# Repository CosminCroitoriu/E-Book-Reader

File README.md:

Nume: Croitoriu Cosmin-Mircea  
Grupă: 332CB

# TSC Project - OpenBook E-Book Reader
Overview
-
This diagram illustrates the hardware architecture of the OpenBook E-Reader, an ESP32-based electronic paper reading device. The system is built around the ESP32-C6-WROOM-1 microcontroller, which interfaces with a 7.5-inch e-Paper display, environmental sensors, and user input buttons.  

***Key Components:*** 

* Core Processing: ESP32-C6 microcontroller with integrated Wi-Fi 6 and BLE 5
* Display: 800×480 resolution e-Paper display connected via SPI
* Sensors: BME688 for temperature, humidity, pressure, and air quality monitoring via I2C
* Power: 2500mAh LiPo battery with fuel gauge and USB-C charging
* Storage: SD card interface for e-book storage via SPI
* Timekeeping: DS3231 RTC with backup power
* User Interface: Buttons via 3xGPIO
* Expansion: QWIIC/Stemma connector for additional peripherals

The firmware is built on FreeRTOS and includes specialized modules for display management, sensor monitoring, battery management, user interface, and e-book rendering. This modular architecture ensures flexible development, easy maintenance, and power-efficient operation—essential for an e-reader device with long battery life requirements.

Power Consumption
-

* In active reading mode (display updated occasionally): ~15-30mA
* In display update mode: ~50-100mA temporarily
* In Wi-Fi active mode: ~120-180mA
* In sleep mode: ~1-5mA
* In deep sleep mode: <50µA

With a 2500mAh battery, the device can operate approximately:

* 100-150 hours in active reading mode (without Wi-Fi)
* 15-20 hours with Wi-Fi constantly active
* Up to 1500 hours (2 months) in deep sleep mode

ESP32-C6 Pin Assignments
-
| Connection Name |   GPIO / Pin Name  | Function  |
|-----------------|------------------|-------------------------------------------------|
| **3V3**         | IO 8             | 3.3V Power line                        |
| **EN (Reset)**  | EN              | Reset Button   |           
| **USB_D-**      | IO12            | USB Data negative, communication  | 
| **USB_D+**      | IO13            | USB Data positive, communication  |
| **Buton Boot**  | IO9             | Bootbutton  |    
| **Buton Change**| IO15            | User input for state changing  |
| **TX (UART)**   | TXD0 / GPIO16   | Serial Transmitter (UART) for communication  |
| **RX (UART)**   | RXD0 / GPIO17   | Serial Receiver (UART) for communication  |
| **SCK (SPI)**   | IO6             | SPI Clock for clock synchronization |
| **MOSI (SPI)**  | IO7             | Transmitter between MC and the Flash, SD Card and display |
| **MISO (SPI)**  | IO2             | Receiver between MC and the Flash, SD Card and display |
| **FLASH_CS**    | IO11            | Flash Chip Select |
| **EPD_CS**      | IO10            | Display Chip select |
| **EPD_DC**      | IO5             | Display Command |
| **EPD_RST**     | IO23            | Display Reset |
| **EPD_BUSY**    | IO3             | Busy Display Signal |
| **SDA (I2C)**   | IO21            | Bidirectional Communication RTC, BME688, Battery Gauge |
| **SCL (I2C)**   | IO22            | I2C synchronization |
| **SS_SD**       | IO4             | SD Card Chip Select |
| **I2C_PW**      | IO19            | Power Control on I2C |
| **EPD_3V3_C**   | IO20            | 3.3V Power Line for the Display |
| **32KHZ**       | IO1             | 32kHz Signal Input |
| **INT_RTC**     | IO0             | RTC DS3231 Interrupt |
| **RTC_RST**     | IO18            | External Reset RTC | 

Bill of Materials
-

| Component | Value | Assigned Part | Where to buy | Datasheet |
| ---------- | --------- | --------- | ---------- | ----- |
| Resistor | 15	$\Omega$ | R_CAPACITOR | [Buy](https://ro.mouser.com/ProductDetail/YAGEO/RT0402FRE0715RL?qs=BXCcY9r%252B08DFFpLSkPOIqQ%3D%3D) | [Datasheet](https://ro.mouser.com/datasheet/2/447/PYu_RT_1_to_0_01_RoHS_L_15-3461507.pdf) |
| Resistor | 200 $\Omega$ | R1_BAT | [Buy](https://ro.mouser.com/ProductDetail/Vishay-Beyschlag/MCS0402MD2000BE100?qs=3SvaY9RawMJNVte4F12%252BZQ%3D%3D) | [Datasheet](https://www.vishay.com/doc?28952) |
| Resistor | 100k $\Omega$ | R_PWRUSB | [Buy](https://ro.mouser.com/ProductDetail/Vishay-Beyschlag/MCT0603PD1003DP500?qs=5aG0NVq1C4wWAn8Ei3OpZA%3D%3D) | [Datasheet](https://www.vishay.com/doc?28916) |
| Resistor | 10k $\Omega$ | R1, R1_PINH1, R1_PINH2, R2-PINH1, R2_PINH2, R4, R5, R6, R7, R8, R9, R10, R_BOOT, R_CHANGE, R_CL1, R_RESET | [Buy](https://ro.mouser.com/ProductDetail/Vishay-Beyschlag/MCS0402MD1002BE000?qs=17u8i%2FzlE8%2F9BrAaXkMk1w%3D%3D) | [Datasheet](https://www.vishay.com/doc?28952) |
| Resistor | 0.47 $\Omega$ | R3 | [Buy](https://ro.mouser.com/ProductDetail/SEI-Stackpole/CSR0402JKR470?qs=IPgv5n7u5QawIB6nBEt8wA%3D%3D) | [Datasheet](https://ro.mouser.com/datasheet/2/385/SEI_CSR_CSRN-3077593.pdf) |
| Resistor |  2k $\Omega$ | R2_BAT |[Buy](https://ro.mouser.com/ProductDetail/Vishay-Beyschlag/MCS04020C2001FE000?qs=wTZ%2FFzl837YG0wIkZJJOwQ%3D%3D) | [Datasheet](https://www.vishay.com/doc?28705) |
| Resistor | 2.2 $\Omega$ | R2 | [Buy](https://ro.mouser.com/ProductDetail/SEI-Stackpole/RMCF0402FT2R20?qs=IPgv5n7u5QbBgyl0jwhwsA%3D%3D) | [Datasheet](https://ro.mouser.com/datasheet/2/385/SEI_RMCF_RMCP-3077565.pdf) |
| Resistor | 5k1 $\Omega$ | R1_USB, R2_USB | [Buy](https://www.venkel.com/part/TFCR0603-16W-K-5690FT) | [Datasheet](https://data.venkel.com/documents/tfcr-series?_gl=1*tdo8m*_ga*NTA1MTc5MTcyLjE3NDM4OTMzNjc.*_ga_JRKGBZNVM8*MTc0Mzg5MzM2Ni4xLjAuMTc0Mzg5MzM2OC41OC4wLjA.) |
| Capacitor | 10uF | C6 | [Buy](https://ro.mouser.com/ProductDetail/Samsung-Electro-Mechanics/CL10A106KQ8NNNL?qs=xZ%2FP%252Ba9zWqaes9JKSsob2Q%3D%3D) | [Datasheet](https://ro.mouser.com/datasheet/2/585/MLCC-1837944.pdf) |
| Capacitor | 1uF/50V | EPD_C3 | [Buy](https://ro.mouser.com/ProductDetail/KYOCERA-AVX/06035D105MAT2A?qs=k4kUdCzLgS5%252BURKe1SOIeQ%3D%3D) | [Datasheet](https://ro.mouser.com/datasheet/2/40/cx5r_KGM-3223198.pdf) |
| Capacitor | 4.7uF | C1_BAT, C1_BAT1, C2_BAT, C2_BAT1, C4_USB | [Buy](https://ro.mouser.com/ProductDetail/KYOCERA-AVX/0402ZD475MAT2A?qs=NBFAU1oqP4W4U2PCPHI0sg%3D%3D) | [Datasheet](https://ro.mouser.com/datasheet/2/40/cx5r_KGM-3223198.pdf) |
| Capacitor | 100nF | C1, C2, C3_USB, C5, C7, C8, C9, C_DELAY | [Buy](https://ro.mouser.com/ProductDetail/KYOCERA-AVX/06033G104ZAT2A?qs=NXubJDmysXJMPmHfVo6Z%252BA%3D%3D) | [Datasheet](https://ro.mouser.com/datasheet/2/40/KGM_Y5V-3223189.pdf) |
| PFMF.050.1 | - | PFMF.050.1 | [Buy](https://ro.mouser.com/ProductDetail/Schurter/PFMF.050.2?qs=1auRipcfynCums5v1iucSA%3D%3D) |  [Datasheet](https://ro.mouser.com/datasheet/2/358/typ_PFMF-1275918.pdf) |
| USB4110-GF-A | - | J2 | [Buy](https://ro.mouser.com/ProductDetail/GCT/USB4110-GF-A?qs=KUoIvG%2F9IlYiZvIXQjyJeA%3D%3D) | [Datasheet](https://ro.mouser.com/datasheet/2/837/GCT_USB4110_Product_Drawing___20k_cycles-3455479.pdf) |
| USBLC6-2SC6Y | - | D1 | [Buy](https://ro.mouser.com/ProductDetail/STMicroelectronics/USBLC6-2SC6Y?qs=gNDSiZmRJS%2FOgDexvXkdow%3D%3D) | [Datasheet](https://ro.mouser.com/datasheet/2/389/usblc6_2sc6y-1852505.pdf) |
| SD0805S020S1R0 | - | D2, D7| [Buy](https://ro.mouser.com/ProductDetail/KYOCERA-AVX/SD0805S020S1R0?qs=jCA%252BPfw4LHbpkAoSnwrdjw%3D%3D) | [Datasheet](https://ro.mouser.com/datasheet/2/40/schottky-3165252.pdf) |
| DMG2305UX-7 | - | Q1, Q2 | [Buy](https://ro.mouser.com/ProductDetail/Diodes-Incorporated/DMG2305UX-7?qs=L1DZKBg7t5F%2FNBHrjfxC%252Bg%3D%3D) | [Datasheet](https://www.diodes.com/assets/Datasheets/DMG2305UX.pdf) |
| XC6220A331MR-G | - | U5 | [Buy](https://ro.mouser.com/ProductDetail/Torex-Semiconductor/XC6220A331MR-G?qs=AsjdqWjXhJ8ZSWznL1J0gg%3D%3D) | [Datasheet](https://ro.mouser.com/datasheet/2/760/xc6220-3371556.pdf) |
| Capacitor | 100 uF TANT | C_TANT | [Buy](https://ro.mouser.com/ProductDetail/KYOCERA-AVX/TAJW107M010RNJ?qs=Wtp%252Bf%2FAeVqIH8v1VxV%252B1Rg%3D%3D) | [Datasheet](https://ro.mouser.com/datasheet/2/40/TAJ-3165264.pdf) |
| 112A-TAAR-R03_ATTEND | - | J4 | [Buy](https://www.digikey.ro/en/products/detail/attend-technology/112A-TAAR-R03/17633923) | [Datasheet](https://www.attend.com.tw/data/download/file/112A-TAAR-R03_Spec.pdf)
| ESP32-C6-WROOM-1-N8 | - | U1 | [Buy](https://ro.mouser.com/ProductDetail/Espressif-Systems/ESP32-C6-WROOM-1-N8?qs=8Wlm6%252BaMh8ST02Gmwp74cw%3D%3D) | [Datasheet](https://ro.mouser.com/datasheet/2/891/Espressif_ESP32_C6_WROOM_1__Datasheet_V0_1_PRELIMI-3239987.pdf) |
| MCP73831 | - | U7 | [Buy](https://ro.mouser.com/ProductDetail/Microchip-Technology/MCP73831T-2ACI-OT?qs=yUQqVecv4qvbBQBGbHx0Mw%3D%3D) | [Datasheet](https://ro.mouser.com/datasheet/2/268/MCP73831_Family_Data_Sheet_DS20001984H-3441711.pdf) |
| CHG_LED | - | CHG_LED | [Buy](https://store.comet.srl.ro/Catalogue/Product/40478/) | [Datasheet](https://www.snapeda.com/parts/KP-1608SURCK/Kingbright/datasheet/) |
| SI1308EDL-T1-GE3 | - | Q3 | [Buy](https://ro.mouser.com/ProductDetail/Vishay-Semiconductors/SI1308EDL-T1-GE3?qs=bX1%252BNvsK%2FBramh9tgpOaEw%3D%3D) | [Datasheet](https://www.vishay.com/doc?63399) |
| MBR0530 | - | D3, D4, D5 | [Buy](https://ro.mouser.com/ProductDetail/Micro-Commercial-Components-MCC/MBR0530-T?qs=9VyI4qLX4NTSXkb9ynzJnA%3D%3D) | [Datasheet](https://ro.mouser.com/datasheet/2/258/mcc_mbr0520~mbr0560sod123-1179695.pdf) |
| Power Inductor | 68uH | L1 | [Buy](https://ro.mouser.com/ProductDetail/Wurth-Elektronik/744043680?qs=PGXP4M47uW6VkZq%252BkzjrHA%3D%3D) | [Datasheet](https://www.we-online.com/components/products/datasheet/744043680.pdf) |
| FH34SRJ-24S-0.5SH | - | J1 | [Buy](https://ro.mouser.com/ProductDetail/Hirose-Connector/FH34SRJ-24S-0.5SH99?qs=vcbW%252B4%252BSTIpKBl5ap9J8Fw%3D%3D) | [Datasheet](https://ro.mouser.com/datasheet/2/185/FH34SRJ_24S_0_5SH_99__CL0580_1255_6_99_2DDrawing_0-1615044.pdf) |
| BME688 Sensor | - | U8 | [Buy](https://ro.mouser.com/ProductDetail/Bosch-Sensortec/BME688?qs=IS%252B4QmGtzzqQoVDscqwx3A%3D%3D) | [Datasheet](https://ro.mouser.com/datasheet/2/783/bst_bme688_fl000-2307034.pdf) |
| BD5229G-TR | - | U6 |[Buy](https://ro.mouser.com/ProductDetail/ROHM-Semiconductor/BD5229G-TR?qs=4kLU8WoGk0vvnhrrYwdszw%3D%3D) | [Datasheet](https://fscdn.rohm.com/en/products/databook/datasheet/ic/power/voltage_detector/bd52xxg-e.pdf) |
| PTS841 Button | - | BOOT_BUTTON, CHANGE_BUTTON, RESET_BUTTON | [Buy](https://ro.mouser.com/ProductDetail/CK/PTS841-ESD-GKP-SMTR-LFS?qs=d0WKAl%252BL4KbeUlwuiSQZWA%3D%3D) | [Datasheet](https://www.ckswitches.com/media/2805/pts841.pdf) |
| MAX17048G+T10 | - | U2 | [Buy](https://ro.mouser.com/ProductDetail/Analog-Devices-Maxim-Integrated/MAX17048G%2bT10?qs=D7PJwyCwLAoGnnn8jEPRBQ%3D%3D) | [Datasheet](https://ro.mouser.com/datasheet/2/609/MAX17048_MAX17049-3469099.pdf) |
| W25Q512JVEIQ | - | U4 | [Buy](https://ro.mouser.com/ProductDetail/Winbond/W25Q512JVEIQ?qs=l7cgNqFNU1jw6svr3at6tA%3D%3D) | [Datasheet](https://ro.mouser.com/datasheet/2/949/Winbond_W25Q512JV_Datasheet-3240039.pdf) |
| PGB1010603MR | - | D6, D8, D9, D10, D11, D12 | [Buy](https://ro.mouser.com/ProductDetail/Littelfuse/PGB1010603MRHF?qs=KvZd0dN2Zg%2FuIq6icj%252BGKA%3D%3D) | [Datasheet](https://www.littelfuse.com/media?resourcetype=datasheets&itemid=8a337998-d54d-466b-be4e-dc5bcd1f9321&filename=littelfuse_pulseguard_pgb1_datasheet.pdf) |
| QWIIC_RIGHT_ANGLE | - | J3 | [Buy](https://ro.mouser.com/ProductDetail/GCT/USB4110-GF-A?qs=KUoIvG%2F9IlYiZvIXQjyJeA%3D%3D) | [Datasheet](https://ro.mouser.com/datasheet/2/837/GCT_USB4110_Product_Drawing___20k_cycles-3455479.pdf) |
| DS3231SN | - | U3 | [Buy](https://ro.mouser.com/ProductDetail/Analog-Devices-Maxim-Integrated/DS3231SN?qs=ffX8NcjNb2RmKAb9wAk9Ug%3D%3D) | [Datasheet](https://ro.mouser.com/datasheet/2/609/DS3231-3421123.pdf) |
| CPH3225A | - | C_SUPERCAP | [Buy](https://ro.mouser.com/ProductDetail/Seiko-Semiconductors/CPH3225A?qs=3etwrb1wR%252BhUOph6lAO7eg%3D%3D) | [Datasheet](https://ro.mouser.com/datasheet/2/360/Seiko_Instruments_MicroBattery_E_20230330_2024Jan_-3561061.pdf) |

Design Considerations
-

* The modular design allows for individual component updates and easy problem diagnosis
* Using a single LDO regulator to generate 3.3V for the entire board simplifies the power design
* Battery charging is done through the USB-C port, ensuring wide compatibility
* The environmental sensors allow for monitoring the conditions in which the device is used and can be used to alert the user about unfavorable conditions
* Used a predefined 3D model for the screen. Source: https://grabcad.com/library/7-5in-e-ink-display-assortment-1

PCB Observations
-

* PCB Dieletctric layer has been reduced from 1.6mm to 1mm to fit in the case.
* Via Stitching has been applied around the MC, so the impedance of the ground plane is lowered.

Errors and Warnings
- 
* The Board Outline Clearence errors were all approved, as every component was matching the placement in the given document.
* Unconnected Lines warnings are a bug from Fusion, as everytime I try to remove them, the error reappears. 
* Copper Width errors for the inductor were approved as the model matched the one in the givne scheme.

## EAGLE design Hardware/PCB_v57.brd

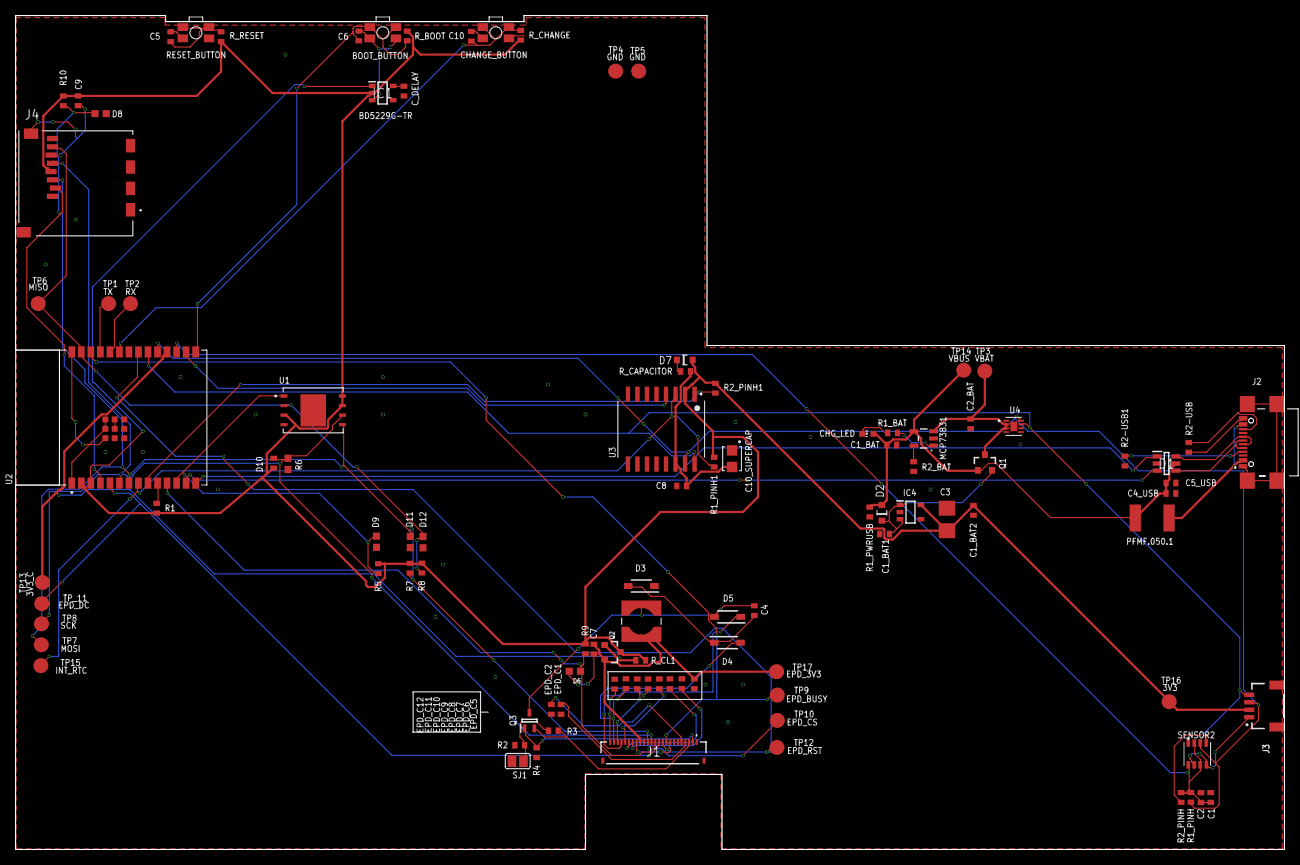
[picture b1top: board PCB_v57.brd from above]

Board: 2 copper layers, 169.2 x 111.2 mm, 103 parts (0 on the bottom side), 56 nets.

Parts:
BOOT_BUTTON: BUTTON_CUSYOMV1; MYBUTTON
C1, C2, C4_USB, C6, C8, C9, C10: 100nF; EAGLE-LTSPICE_C0402
C1_BAT, C1_BAT1, C1_BAT2, C2_BAT, C5_USB: 4.7uF; EAGLE-LTSPICE_C0402
C3: 100uF TANT; RCL_CT3528
C4: 4.7uF/25V; EAGLE-LTSPICE_C0402
C5: 1uF; EAGLE-LTSPICE_C0402
C7: 10uF; EAGLE-LTSPICE_C0402
C10_SUPERCAP: CPH3225A; CAPCP3225X100N
CHANGE_BUTTON: BUTTON_CUSYOMV1; MYBUTTON
CHG_LED: ADAFRUIT_CHIP-LED0603
C_DELAY: 100nF; EAGLE-LTSPICE_C0402
D1: USBLC6-2SC6Y; SOT95P280X145-6N
D2, D7: ESP32_WROVER_AVX---SD0805S020S1R0_AVX_SD0805S020S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; ESP32_WROVER_AVX---SD0805S020S1R0_AVX_SD0805S020S1R0_0
D3, D4, D5: MBR0530; SOD3716X135N
D6, D8, D9, D10, D11, D12: PGB1010603MR; DIOC1608X36N
EPD_C1, EPD_C2, EPD_C6, EPD_C7, EPD_C8, EPD_C9, EPD_C10, EPD_C11, EPD_C12: 1uF/50V; EAGLE-LTSPICE_C0402
EPD_C5: 01.uF/50V; EAGLE-LTSPICE_C0402
IC1: BD5229G-TR; SOT95P280X125-5N
IC4: XC6220A331MR-G; SOT95P280X120-5N
J1: FH34SRJ-24S-0.5SH_99_; FH34SRJ24S05SH99
J2: SAMACSYS_PARTS_USB4110-GF-A; SAMACSYS_PARTS_USB4110GFA
J3: QWIIC_RIGHT_ANGLE; JST04_1MM_RA
J4: 112A-TAAR-R03_ATTEND; 112ATAARR03ATTEND
L1: 68uH; IND_4828-WE-TPC_WRE
MCP73831: ESP32_WROVER_SPARKFUN-IC-POWER_MCP73831; ESP32_WROVER_SPARKFUN-IC-POWER_SOT23-5
PFMF.050.1: ESP32C6_VARISTORCN1812; ESP32C6_VARISTOR_CT/CN1812
Q1, Q2: 20V/4.2A/52mΩ/1.4W; ESP32_WROVER_SPARKFUN-DISCRETESEMI_SOT23-3
Q3: SI1308EDL-T1-GE3; SOT65P210X110-3N
R1, R1_PINH, R2_PINH, R4: 10k; ESP32_WROVER_EAGLE-LTSPICE_R0402
R1_BAT: 200; ESP32_WROVER_EAGLE-LTSPICE_R0402
R1_PINH1, R2_PINH1, R5, R6, R7, R8, R9, R10: 10K; ESP32_WROVER_EAGLE-LTSPICE_R0402
R1_PWRUSB: 100K; ESP32_WROVER_EAGLE-LTSPICE_R0402
R2: 2.2; ESP32_WROVER_EAGLE-LTSPICE_R0402
R2-USB, R2-USB1: 5k1; ESP32_WROVER_EAGLE-LTSPICE_R0402
R2_BAT: 2K; ESP32_WROVER_EAGLE-LTSPICE_R0402
R3: 0.47; ESP32_WROVER_EAGLE-LTSPICE_R0402
RESET_BUTTON: BUTTON_CUSYOMV1; MYBUTTON
R_BOOT: 10K; ESP32_WROVER_EAGLE-LTSPICE_R0402
R_CAPACITOR: 15; ESP32_WROVER_EAGLE-LTSPICE_R0402
R_CHANGE: 10K; ESP32_WROVER_EAGLE-LTSPICE_R0402
R_CL1: 10k; ESP32_WROVER_EAGLE-LTSPICE_R0402
R_RESET: 10K; ESP32_WROVER_EAGLE-LTSPICE_R0402
SENSOR2: ESP32_WROVER_BME680_BME680; ESP32_WROVER_BME680_PSON80P300X300X100-8N
SJ1: SJ
TP1, TP2, TP3, TP4, TP5, TP6, TP7, TP8, TP9, TP10, TP12, TP13, TP14, TP15, TP16, TP17: TPTP20R; TP20R
TP_11: TPTP20R; TP20R
U1: W25Q512JVEIQ; SON127P600X800X80-9N
U2: ESP32-C6-WROOM-1-N8; XCVR_ESP32-C6-WROOM-1-N8
U3: DS3231SN#; SOIC127P1032X265-16N
U4: MAX17048G+T10; SON50P200X200X80-9N

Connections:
3V3: C1_BAT2.2, C3.+, C9.1, D7.2, IC1.2, IC4.5, J3.2, J4.P4, Q2.3, R1.2, R1_PINH1.2, R2_PINH1.2, R5.2, R6.2, R7.2, R8.2, R9.2, R10.2, R_BOOT.2, R_CHANGE.2, R_CL1.2, R_RESET.2, TP16.TP, U1.3, U1.7, U1.8, U2.2, U3.2
32KHZ: R2_PINH1.1, U2.9, U3.1
DN: D1.4, J2.A7, J2.B7
DP: D1.6, J2.A6, J2.B6
EPD_3V3: C7.1, EPD_C5.2, J1.15, J1.16, L1.2, Q2.2, TP17.TP
EPD_3V3_C: Q2.1, R_CL1.1, TP13.TP, U2.18
EPD_BUSY: J1.9, TP9.TP, U2.26
EPD_CS: D6.2, J1.12, R9.1, TP10.TP, U2.11
EPD_DC: J1.11, TP_11.TP, U2.5
EPD_RST: J1.10, TP12.TP, U2.21
FLASH_CS: D9.2, R5.1, U1.1, U2.12
GDR: J1.2, Q3.1, R4.2
GND: BOOT_BUTTON.1, BOOT_BUTTON.2, C1.2, C1_BAT.2, C1_BAT1.1, C1_BAT2.1, C2.2, C2_BAT.2, C3.-, C4_USB.2, C5.2, C5_USB.2, C6.2, C7.2, C8.2, C9.2, C10.2, C10_SUPERCAP.1, CHANGE_BUTTON.1, CHANGE_BUTTON.2, C_DELAY.2, D1.2, D3.1, D6.1, D8.1, D9.1, D10.1, D11.1, D12.1, EPD_C1.1, EPD_C2.1, EPD_C5.1, EPD_C6.1, EPD_C7.1, EPD_C8.1, EPD_C9.1, EPD_C10.1, EPD_C11.1, EPD_C12.1, IC1.3, IC4.2, J1.8, J1.17, J1.MP1, J1.MP2, J2.A1, J2.A12, J2.B1, J2.B12, J2.MP1, J2.MP2, J2.MP3, J2.MP4, J3.1, J4.G1, J4.G2, J4.G3, J4.G4, J4.P6, MCP73831.2, R1_PWRUSB.1, R2.1, R2-USB.2, R2-USB1.1, R2_BAT.1, R4.1, RESET_BUTTON.1, RESET_BUTTON.2, SENSOR2.1, SENSOR2.5, SENSOR2.7, SJ1.1, TP4.TP, TP5.TP, U1.4, U1.9, U2.1, U2.28, U2.29_1, U2.29_2, U2.29_3, U2.29_4, U2.29_5, U2.29_6, U2.29_7, U2.29_8, U2.29_9, U3.13, U4.1, U4.4, U4.6, U4.9
GPIO8: R1.1, U2.10
I2C_PW: C1.1, C2.1, R1_PINH.2, R2_PINH.2, SENSOR2.2, SENSOR2.6, SENSOR2.8, U2.17
INT_RTC: R1_PINH1.1, TP15.TP, U2.8, U3.3
IO/BOOT: BOOT_BUTTON.3, BOOT_BUTTON.4, C6.1, R_BOOT.1, U2.15
IO/CHANGE: C10.1, CHANGE_BUTTON.3, CHANGE_BUTTON.4, R_CHANGE.1, U2.23
MISO: D12.2, J4.P7, R8.1, TP6.TP, U1.2, U2.27
MOSI: D11.2, J1.14, J4.P3, R7.1, TP7.TP, U1.5, U2.7
unnamed: J2.A5, R2-USB1.2
unnamed: J2.B5, R2-USB.1
unnamed: C1_BAT1.2, D2.1, IC4.1, IC4.3, Q1.2
unnamed: CHG_LED.C, R1_BAT.1
unnamed: MCP73831.1, R1_BAT.2
unnamed: C4.1, D3.2, D4.1
unnamed: MCP73831.5, R2_BAT.2
unnamed: EPD_C12.2, J1.24
unnamed: C_DELAY.1, IC1.5
unnamed: EPD_C10.2, J1.22
unnamed: C5.1, RESET_BUTTON.3, RESET_BUTTON.4, R_RESET.1
unnamed: EPD_C8.2, J1.20
unnamed: EPD_C7.2, J1.19
unnamed: EPD_C6.2, J1.18
unnamed: D7.1, R_CAPACITOR.1
unnamed: EPD_C2.2, J1.5
unnamed: EPD_C1.2, J1.4
PREVGH: D5.1, EPD_C9.2, J1.21
PREVGL: D4.2, EPD_C11.2, J1.23
RESE: J1.3, Q3.2, R3.2
RESE': R2.2, R3.1, SJ1.2
RESET: IC1.1, U2.3
RTC_RST: U2.16, U3.4
RX: TP2.TP, U2.24
SCK: D10.2, J1.13, J4.P5, R6.1, TP8.TP, U1.6, U2.6
SCL: J3.4, R2_PINH.1, SENSOR2.4, U2.20, U3.16, U4.7
SDA: J3.3, R1_PINH.1, SENSOR2.3, U2.19, U3.15, U4.8
SRC: C4.2, D5.2, L1.1, Q3.3
SS_SD: D8.2, J4.P2, R10.1, U2.4
TX: TP1.TP, U2.25
USB_D+: D1.1, U2.14
USB_D-: D1.3, U2.13
VBAT: C2_BAT.1, MCP73831.3, Q1.3, TP3.TP, U4.2, U4.3
VBUS: C1_BAT.1, C4_USB.1, C5_USB.1, CHG_LED.A, D1.5, D2.2, MCP73831.4, PFMF.050.1.2, Q1.1, R1_PWRUSB.2, TP14.TP
VRTC: C8.1, C10_SUPERCAP.2, R_CAPACITOR.2, U3.14
VUSB: J2.A4, J2.A9, J2.B4, J2.B9, PFMF.050.1.1

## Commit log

2025-04-06 Create LICENSE
2025-04-06 the end
2025-04-07 Rename README..md to README.md
2025-04-11 Added the last version after the issue fixes
2025-04-16 Added final version of the PCB file.

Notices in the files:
parts and their libraries:
COPYRIGHT: Copyright (C) 2024 Ultra Librarian. All rights reserved.
